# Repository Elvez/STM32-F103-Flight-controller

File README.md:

# STM32-F103-Flight-controller
STM32F103C8T6 based flight controller PCB with MPU6050 I2C onboard.
 
I used KiCAD for the project.
Here are some pictures of the Board.

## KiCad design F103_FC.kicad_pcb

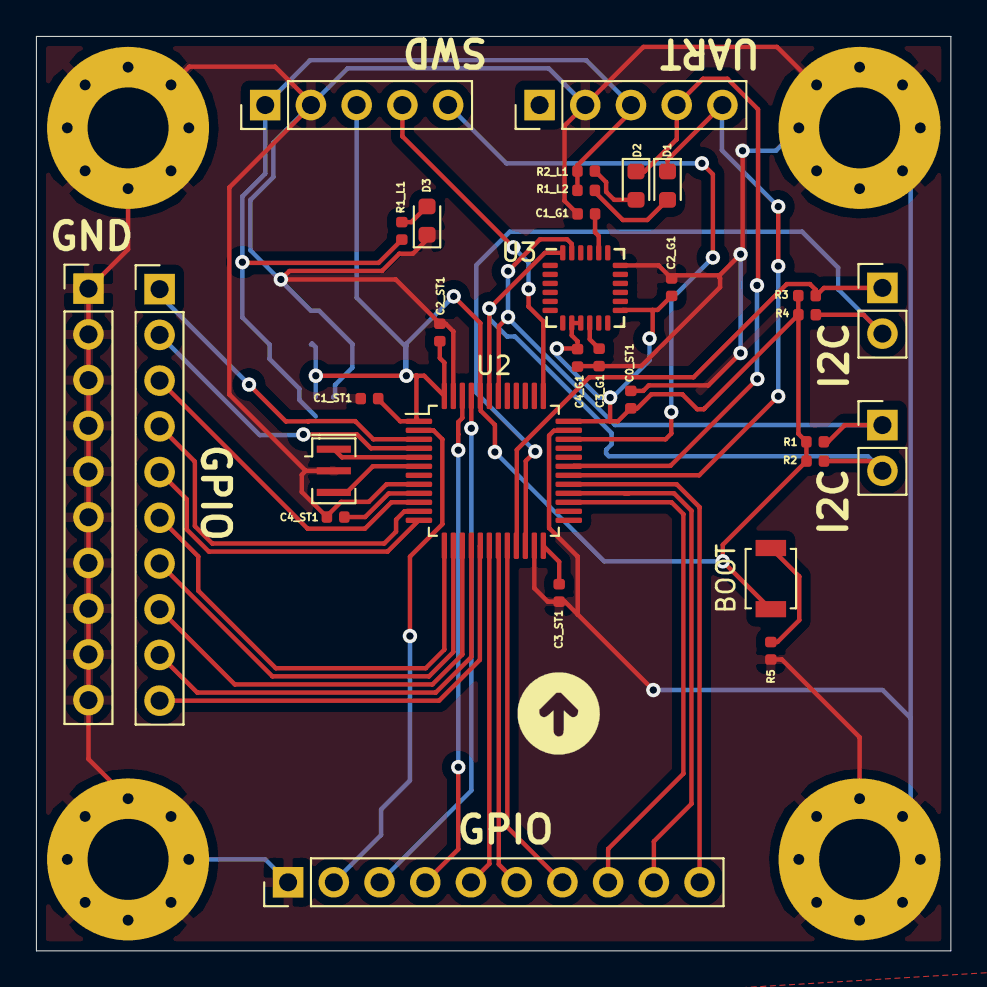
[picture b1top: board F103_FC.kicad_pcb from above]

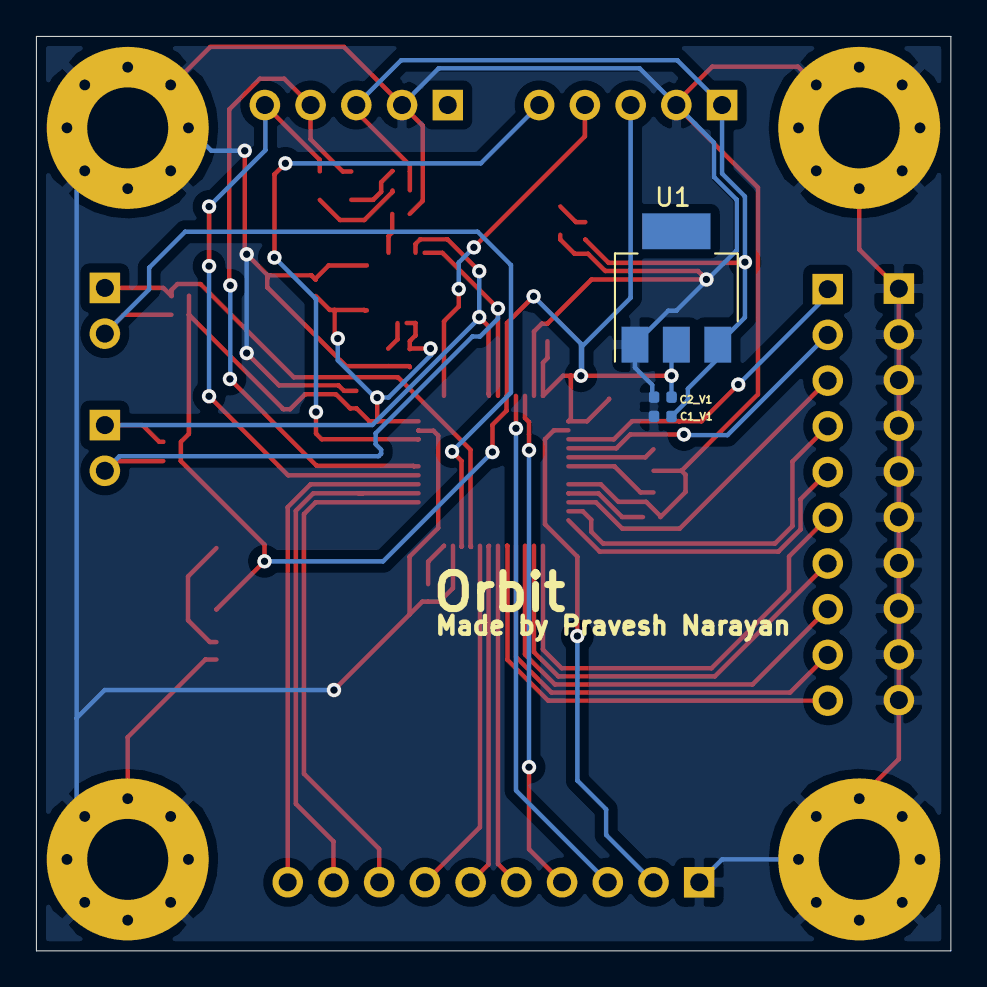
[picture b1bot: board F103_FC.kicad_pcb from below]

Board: 2 copper layers, 50.8 x 50.8 mm, 39 parts (3 on the bottom side), 38 nets.

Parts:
.: LOGO; tt
BOOT: SW_DIP_x01; SW_SPST_B3U-1000P
C0_ST1: 1u; C_0402_1005Metric
C1_G1: 2.2n; C_0402_1005Metric
C1_ST1, C2_ST1, C3_ST1, C4_ST1: 100n; C_0402_1005Metric
C1_V1, C2_V1: 10u; C_0402_1005Metric
C2_G1, C3_G1: 0.1u; C_0402_1005Metric
C4_G1: 10n; C_0402_1005Metric
D1, D2, D3: LED; LED_0603_1608Metric
H1, H2, H3, H4: MountingHole_Pad; MountingHole_4.5mm_Pad_Via
J2, J3, J3#2: Conn_01x10; PinHeader_1x10_P2.54mm_Vertical
J4, J7: Conn_01x05; PinHeader_1x05_P2.54mm_Vertical
J5, J6: Conn_01x02; PinHeader_1x02_P2.54mm_Vertical
R1, R2, R3, R4, R5: 1k; R_0402_1005Metric
R1_L1, R1_L2, R2_L1: 330; R_0402_1005Metric
U1: NCP1117-3.3_SOT223; SOT-223-3_TabPin2
U2: STM32F103C8Tx; LQFP-48_7x7mm_P0.5mm
U3: MPU-6050; InvenSense_QFN-24_4x4mm_P0.5mm
Y1: 16Mhz; Resonator_SMD_muRata_CSTxExxV-3Pin_3.0x1.1mm

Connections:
5V_IN: C1_V1.2, J4.1, J7.3, R1_L1.1, R1_L2.1, R2_L1.1, U1.3
A0: J3#2.3, U2.10
A1: J3#2.4, U2.11
A2: J3#2.5, U2.12
A3: J3#2.6, U2.13
A4: J3#2.7, U2.14
A5: J3#2.8, U2.15
A6: J3#2.9, U2.16
A7: J3#2.10, U2.17
A8: J2.10, U2.29
B0: J2.5, U2.18
B1: J2.6, U2.19
B2: J2.7, U2.20
B8: J2.3, U2.45
B9: J2.4, U2.46
B14: J2.8, U2.27
B15: J2.9, U2.28
BOOT: BOOT.1, C0_ST1.1, C1_ST1.1, C2_G1.2, C2_ST1.1, C2_V1.1, C3_ST1.1, C4_G1.1, C4_ST1.1, J4.3, R1.1, R2.1, R3.1, R4.1, U1.2, U2.1, U2.9, U2.24, U2.36, U2.44, U2.48, U3.8, U3.9, U3.13
C13: J2.2, U2.2
C14: J3#2.1, U2.3
C15: J3#2.2, U2.4
GND: C0_ST1.2, C1_G1.1, C1_ST1.2, C1_V1.1, C2_G1.1, C2_ST1.2, C2_V1.2, C3_G1.2, C3_ST1.2, C4_G1.2, C4_ST1.2, D3.1, H1.1, H2.1, H3.1, H4.1, J2.1, J3.1, J3.2, J3.3, J3.4, J3.5, J3.6, J3.7, J3.8, J3.9, J3.10, J4.2, J7.2, R5.1, U1.1, U2.8, U2.23, U2.35, U2.47, U3.18, Y1.2
unnamed: C1_G1.2, U3.20
unnamed: C3_G1.1, U3.10
unnamed: D1.2, R1_L2.2
unnamed: D2.2, R2_L1.2
unnamed: D3.2, R1_L1.2
unnamed: BOOT.2, R5.2
OSC_IN: U2.5, Y1.1
OSC_OUT: U2.6, Y1.3
RX: D2.1, J7.4, U2.31
SCL1: J6.1, R1.2, U2.42, U3.23
SCL2: J5.1, R3.2, U2.21
SDA1: J6.2, R2.2, U2.43, U3.24
SDA2: J5.2, R4.2, U2.22
SWCLK: J4.4, U2.37
SWDIO: J4.5, U2.34
TX: D1.1, J7.5, U2.30
